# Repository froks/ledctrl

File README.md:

# ledctrlv2.1

ledctrl is a 24-channel controller for led-strips - it uses a stm32f407 to pwm-control 12x QS6K1 MOSFETs for the channels, and a microsd-card slot to store animation/program data.

Prototypes were built and were working, but the project didn't progress any further and was abandoned. 

The modified micropython-version with the custom mappings is missing, but could be easily recreated.

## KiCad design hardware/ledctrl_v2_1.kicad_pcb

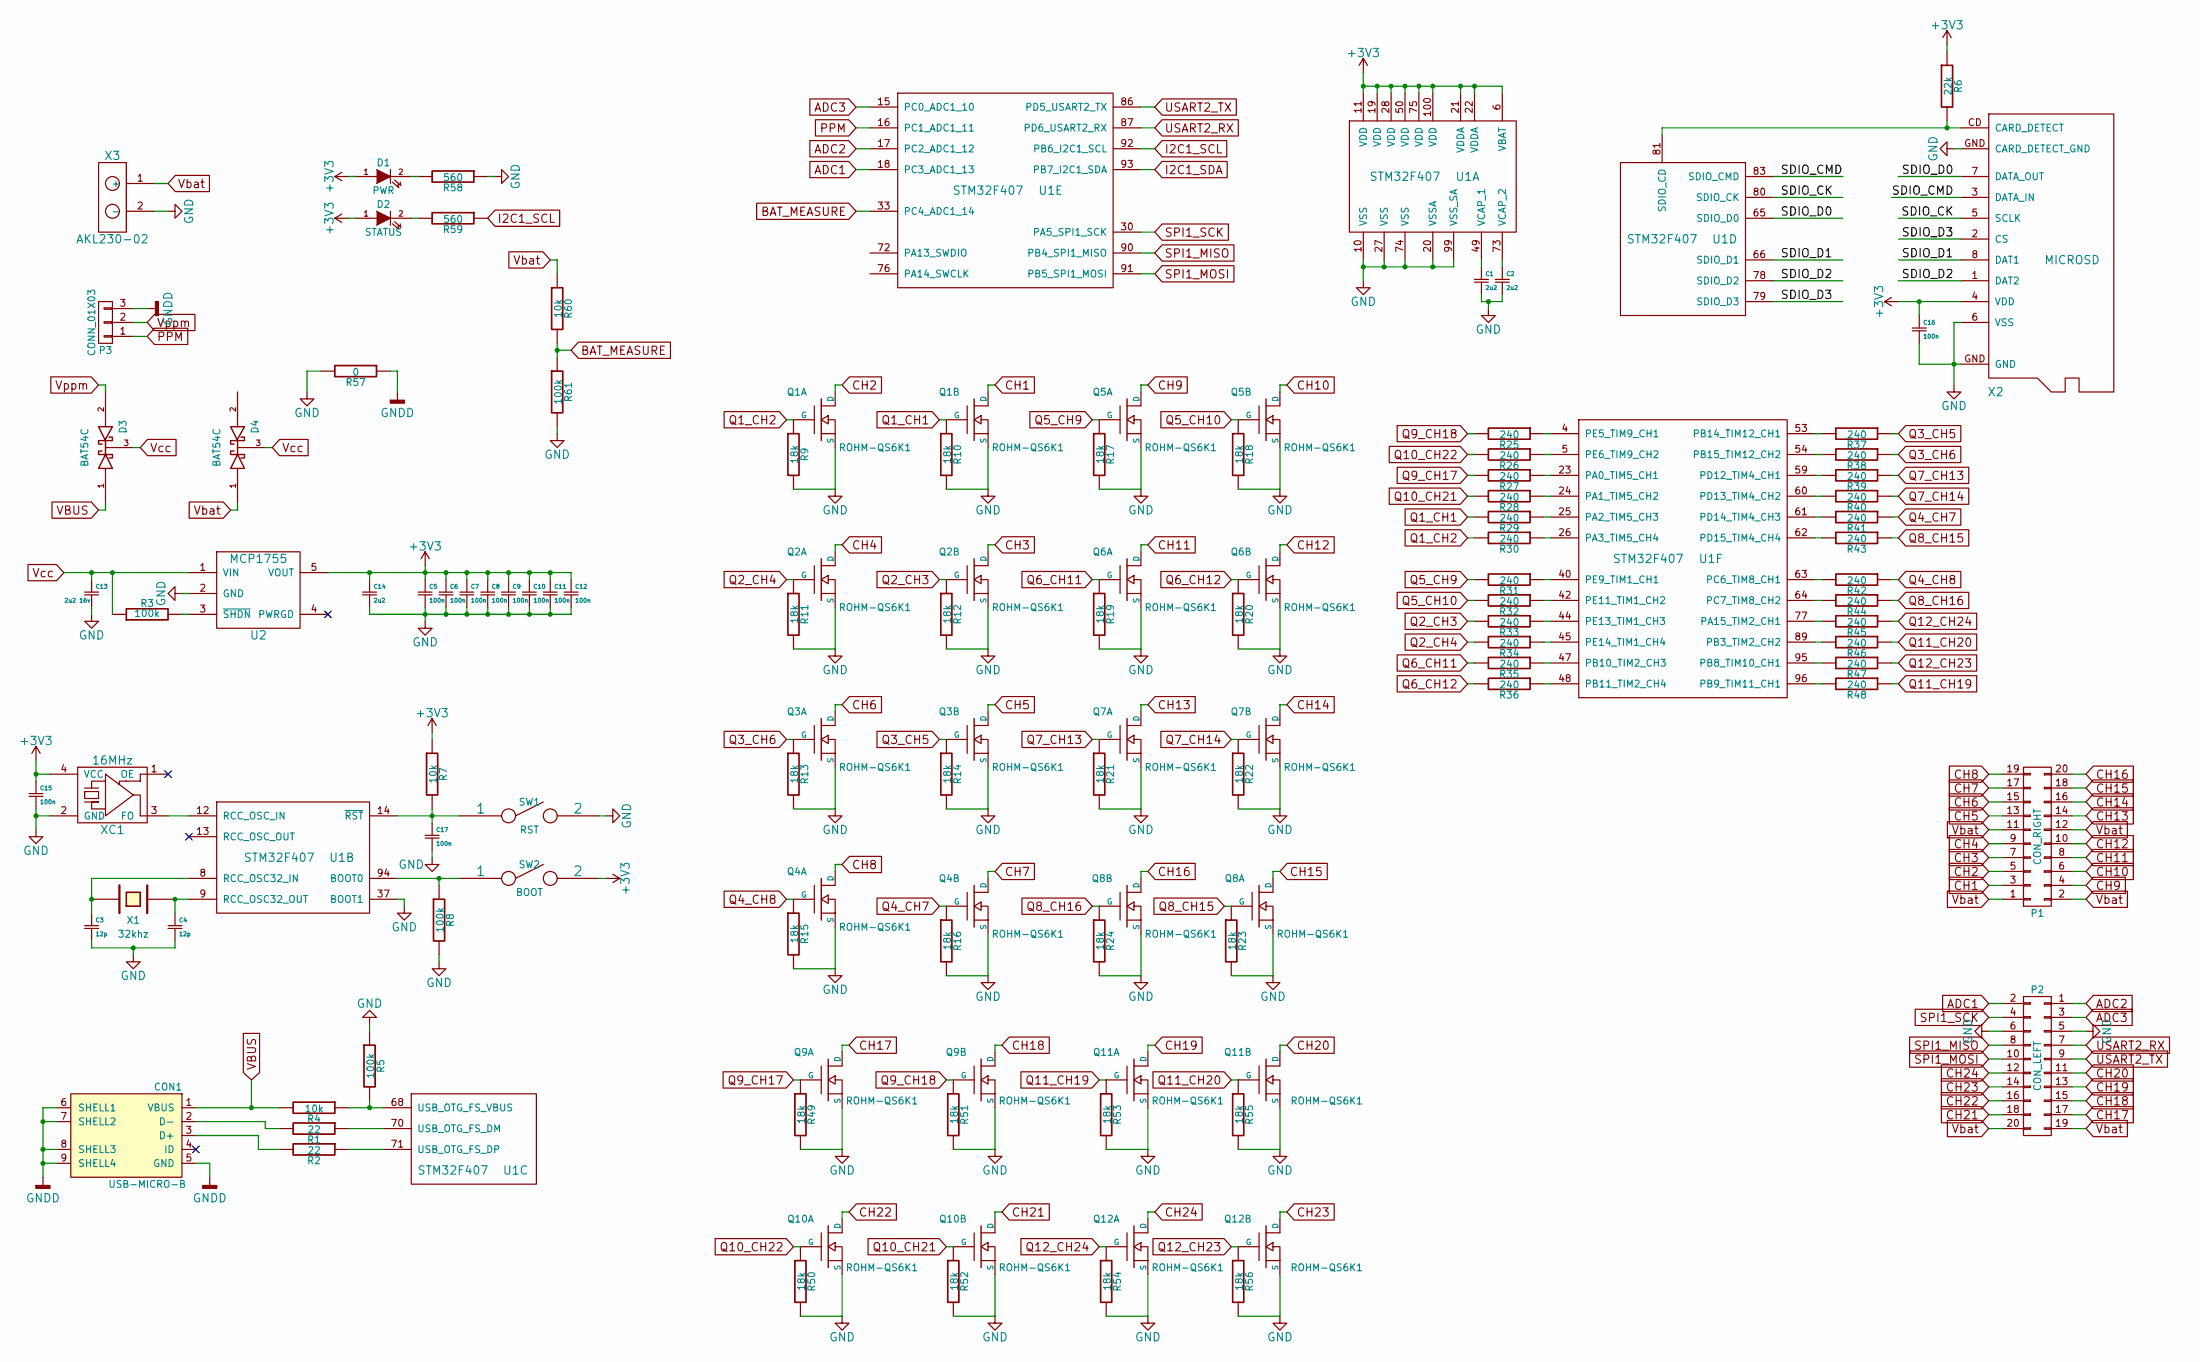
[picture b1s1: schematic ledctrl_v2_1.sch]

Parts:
C1, C2, C14: 2u2; C_0603
C3, C4: 12p; C_0402
C5, C6, C7, C8, C9, C10, C11, C12, C15, C16, C17: 100n; C_0402
C13: 2u2 16v; C_0603
CON1: USB-MICRO-B; MOLEX_473460001
D1: PWR; LED-0603
D2: STATUS; LED-0603
D3, D4: BAT54C; SOT-23
P1: CON_RIGHT; CON_10x2_SIDEWAYS
P2: CON_LEFT; CON_10x2_SIDEWAYS
P3: CONN_01X03; Pin_Header_Angled_1x03
Q1, Q2, Q3, Q4, Q5, Q6, Q7, Q8, Q9, Q10, Q11, Q12: ROHM-QS6K1; TSMT6
R1, R2: 22; R_0402
R3, R5, R8, R61: 100k; R_0402
R4, R7, R60: 10k; R_0402
R6: 22k; R_0402
R9, R10, R11, R12, R13, R14, R15, R16, R17, R18, R19, R20, R21, R22, R23, R24, R49, R50, R51, R52, R53, R54, R55, R56: 18k; R_0402
R25, R26, R27, R28, R29, R30, R31, R32, R33, R34, R35, R36, R37, R38, R39, R40, R41, R42, R43, R44, R45, R46, R47, R48: 240; R_0402
R57: 0; R_0603
R58, R59: 560; R_0402
SW1: RST; TE_1977066-1
SW2: BOOT; TE_1977066-1
U1: STM32F407; LQFP-100_14x14mm_Pitch0.5mm
U2: MCP1755; SOT23-5
X1: 32khz; FC-135
X2: MICROSD; AMP_101-00660-68-6
X3: AKL230-02; AKL235-02_XT60
XC1: 16MHz; ASDMB

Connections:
+3V3: C5.1, C6.1, C7.1, C8.1, C9.1, C10.1, C11.1, C12.1, C14.1, C15.1, C16.1, D1.1 (A), D2.1 (A), R6.1, R7.1, SW2.2, U1.6 (VBAT), U1.11 (VDD), U1.19 (VDD), U1.21 (VDDA), U1.22 (VDDA), U1.28 (VDD), U1.50 (VDD), U1.75 (VDD), U1.100 (VDD), U2.5 (VOUT), X2.4 (VDD), XC1.4 (VCC)
/SDIO_CK: U1.80 (SDIO_CK), X2.5 (SCLK)
/SDIO_CMD: U1.83 (SDIO_CMD), X2.3 (DATA_IN)
/SDIO_D0: U1.65 (SDIO_D0), X2.7 (DATA_OUT)
/SDIO_D1: U1.66 (SDIO_D1), X2.8 (DAT1)
/SDIO_D2: U1.78 (SDIO_D2), X2.1 (DAT2)
/SDIO_D3: U1.79 (SDIO_D3), X2.2 (CS)
ADC1: P2.2, U1.18 (PC3_ADC1_13)
ADC2: P2.1, U1.17 (PC2_ADC1_12)
ADC3: P2.3, U1.15 (PC0_ADC1_10)
BAT_MEASURE: R60.2, R61.1, U1.33 (PC4_ADC1_14)
CH1: P1.3, Q1.4 (D)
CH2: P1.5, Q1.6 (D)
CH3: P1.7, Q2.4 (D)
CH4: P1.9, Q2.6 (D)
CH5: P1.13, Q3.4 (D)
CH6: P1.15, Q3.6 (D)
CH7: P1.17, Q4.4 (D)
CH8: P1.19, Q4.6 (D)
CH9: P1.4, Q5.6 (D)
CH10: P1.6, Q5.4 (D)
CH11: P1.8, Q6.6 (D)
CH12: P1.10, Q6.4 (D)
CH13: P1.14, Q7.6 (D)
CH14: P1.16, Q7.4 (D)
CH15: P1.18, Q8.6 (D)
CH16: P1.20, Q8.4 (D)
CH17: P2.17, Q9.6 (D)
CH18: P2.15, Q9.4 (D)
CH19: P2.13, Q11.6 (D)
CH20: P2.11, Q11.4 (D)
CH21: P2.18, Q10.4 (D)
CH22: P2.16, Q10.6 (D)
CH23: P2.14, Q12.4 (D)
CH24: P2.12, Q12.6 (D)
GND: C1.2, C2.2, C3.2, C4.2, C5.2, C6.2, C7.2, C8.2, C9.2, C10.2, C11.2, C12.2, C13.2, C14.2, C15.2, C16.2, C17.2, P2.5, P2.6, Q1.2 (S), Q1.5 (S), Q2.2 (S), Q2.5 (S), Q3.2 (S), Q3.5 (S), Q4.2 (S), Q4.5 (S), Q5.2 (S), Q5.5 (S), Q6.2 (S), Q6.5 (S), Q7.2 (S), Q7.5 (S), Q8.2 (S), Q8.5 (S), Q9.2 (S), Q9.5 (S), Q10.2 (S), Q10.5 (S), Q11.2 (S), Q11.5 (S), Q12.2 (S), Q12.5 (S), R5.1, R8.2, R9.2, R10.2, R11.2, R12.2, R13.2, R14.2, R15.2, R16.2, R17.2, R18.2, R19.2, R20.2, R21.2, R22.2, R23.2, R24.2, R49.2, R50.2, R51.2, R52.2, R53.2, R54.2, R55.2, R56.2, R57.2, R58.1, R61.2, SW1.2, U1.10 (VSS), U1.20 (VSSA), U1.27 (VSS), U1.37 (BOOT1), U1.74 (VSS), U1.99 (VSS_SA), U2.2 (GND), X2.6 (VSS), X2.GND (CARD_DETECT_GND), X3.2 (-), XC1.2 (GND)
GNDD: CON1.5 (GND), CON1.6 (SHELL1), CON1.7 (SHELL2), CON1.8 (SHELL3), CON1.9 (SHELL4), P3.3, R57.1
I2C1_SCL: R59.1, U1.92 (PB6_I2C1_SCL)
I2C1_SDA: U1.93 (PB7_I2C1_SDA)
unnamed: C1.1, U1.49 (VCAP_1)
unnamed: C2.1, U1.73 (VCAP_2)
unnamed: C3.1, U1.8 (RCC_OSC32_IN), X1.1
unnamed: C4.1, U1.9 (RCC_OSC32_OUT), X1.2
unnamed: C17.1, R7.2, SW1.1, U1.14 (~RST)
unnamed: CON1.2 (D-), R1.2
unnamed: CON1.3 (D+), R2.2
unnamed: D1.2 (K), R58.2
unnamed: D2.2 (K), R59.2
unnamed: R1.1, U1.70 (USB_OTG_FS_DM)
unnamed: R2.1, U1.71 (USB_OTG_FS_DP)
unnamed: R3.2, U2.3 (~SHDN)
unnamed: R4.1, R5.2, U1.68 (USB_OTG_FS_VBUS)
unnamed: R6.2, U1.81 (SDIO_CD), X2.CD (CARD_DETECT)
unnamed: R8.1, SW2.1, U1.94 (BOOT0)
unnamed: R25.1, U1.4 (PE5_TIM9_CH1)
unnamed: R26.1, U1.5 (PE6_TIM9_CH2)
unnamed: R27.1, U1.23 (PA0_TIM5_CH1)
unnamed: R28.1, U1.24 (PA1_TIM5_CH2)
unnamed: R29.1, U1.25 (PA2_TIM5_CH3)
unnamed: R30.1, U1.26 (PA3_TIM5_CH4)
unnamed: R31.1, U1.40 (PE9_TIM1_CH1)
unnamed: R32.1, U1.42 (PE11_TIM1_CH2)
unnamed: R33.1, U1.44 (PE13_TIM1_CH3)
unnamed: R34.1, U1.45 (PE14_TIM1_CH4)
unnamed: R35.1, U1.47 (PB10_TIM2_CH3)
unnamed: R36.1, U1.48 (PB11_TIM2_CH4)
unnamed: R37.2, U1.53 (PB14_TIM12_CH1)
unnamed: R38.2, U1.54 (PB15_TIM12_CH2)
unnamed: R39.2, U1.59 (PD12_TIM4_CH1)
unnamed: R40.2, U1.60 (PD13_TIM4_CH2)
unnamed: R41.2, U1.61 (PD14_TIM4_CH3)
unnamed: R42.2, U1.63 (PC6_TIM8_CH1)
unnamed: R43.2, U1.62 (PD15_TIM4_CH4)
unnamed: R44.2, U1.64 (PC7_TIM8_CH2)
unnamed: R45.2, U1.77 (PA15_TIM2_CH1)
unnamed: R46.2, U1.89 (PB3_TIM2_CH2)
unnamed: R47.2, U1.95 (PB8_TIM10_CH1)
unnamed: R48.2, U1.96 (PB9_TIM11_CH1)
unnamed: U1.12 (RCC_OSC_IN), XC1.3 (FO)
PPM: P3.1, U1.16 (PC1_ADC1_11)
Q1_CH1: Q1.3 (G), R10.1, R29.2
Q1_CH2: Q1.1 (G), R9.1, R30.2
Q2_CH3: Q2.3 (G), R12.1, R33.2
Q2_CH4: Q2.1 (G), R11.1, R34.2
Q3_CH5: Q3.3 (G), R14.1, R37.1
Q3_CH6: Q3.1 (G), R13.1, R38.1
Q4_CH7: Q4.3 (G), R16.1, R41.1
Q4_CH8: Q4.1 (G), R15.1, R42.1
Q5_CH9: Q5.1 (G), R17.1, R31.2
Q5_CH10: Q5.3 (G), R18.1, R32.2
Q6_CH11: Q6.1 (G), R19.1, R35.2
Q6_CH12: Q6.3 (G), R20.1, R36.2
Q7_CH13: Q7.1 (G), R21.1, R39.1
Q7_CH14: Q7.3 (G), R22.1, R40.1
Q8_CH15: Q8.1 (G), R23.1, R43.1
Q8_CH16: Q8.3 (G), R24.1, R44.1
Q9_CH17: Q9.1 (G), R27.2, R49.1
Q9_CH18: Q9.3 (G), R25.2, R51.1
Q10_CH21: Q10.3 (G), R28.2, R52.1
Q10_CH22: Q10.1 (G), R26.2, R50.1
Q11_CH19: Q11.1 (G), R48.1, R53.1
Q11_CH20: Q11.3 (G), R46.1, R55.1
Q12_CH23: Q12.3 (G), R47.1, R56.1
Q12_CH24: Q12.1 (G), R45.1, R54.1
SPI1_MISO: P2.8, U1.90 (PB4_SPI1_MISO)
SPI1_MOSI: P2.10, U1.91 (PB5_SPI1_MOSI)
SPI1_SCK: P2.4, U1.30 (PA5_SPI1_SCK)
USART2_RX: P2.7, U1.87 (PD6_USART2_RX)
USART2_TX: P2.9, U1.86 (PD5_USART2_TX)
VBUS: CON1.1 (VBUS), D3.1 (Anode), R4.2
Vbat: D4.1 (Anode), P1.1, P1.2, P1.11, P1.12, P2.19, P2.20, R60.1, X3.1 (+)
Vcc: C13.1, D3.3 (AK), D4.3 (AK), R3.1, U2.1 (VIN)
Vppm: D3.2 (cathode), P3.2

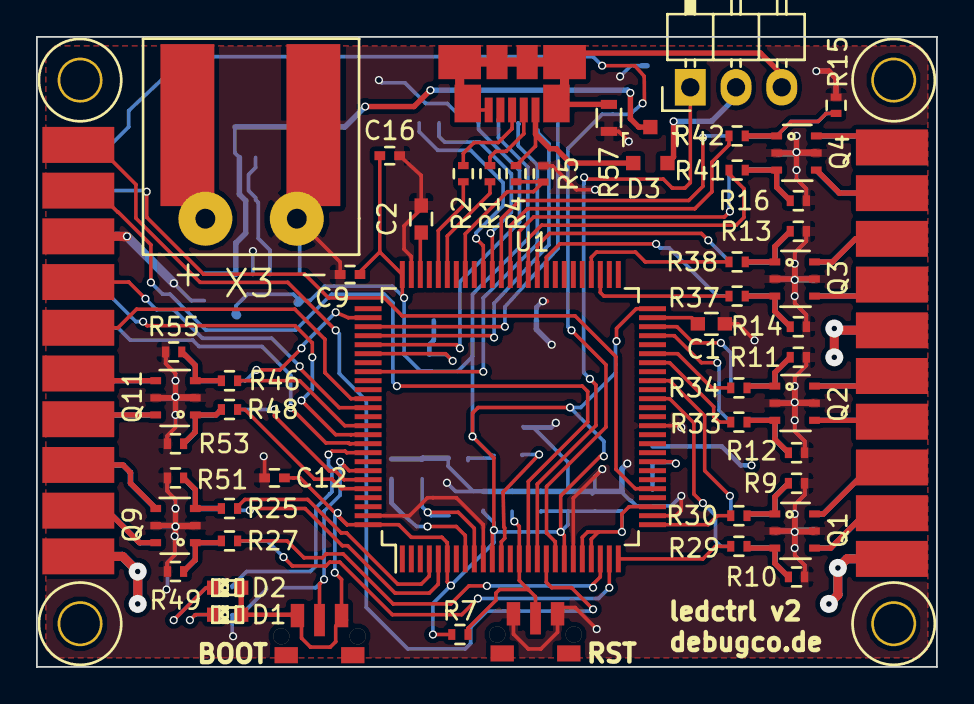
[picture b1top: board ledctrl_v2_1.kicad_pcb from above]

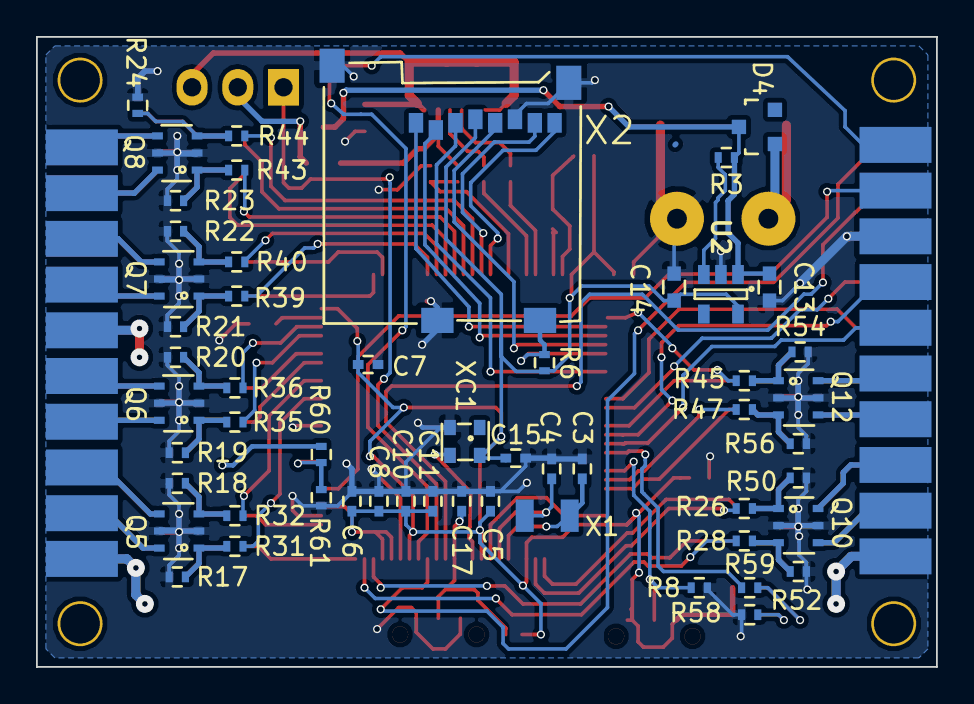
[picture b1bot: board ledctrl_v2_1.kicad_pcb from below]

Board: 4 copper layers, 50.0 x 35.0 mm, 107 parts (54 on the bottom side), 112 nets.

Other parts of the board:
1pin: VAL**; 1pin

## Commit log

2020-12-24 Create LICENSE
